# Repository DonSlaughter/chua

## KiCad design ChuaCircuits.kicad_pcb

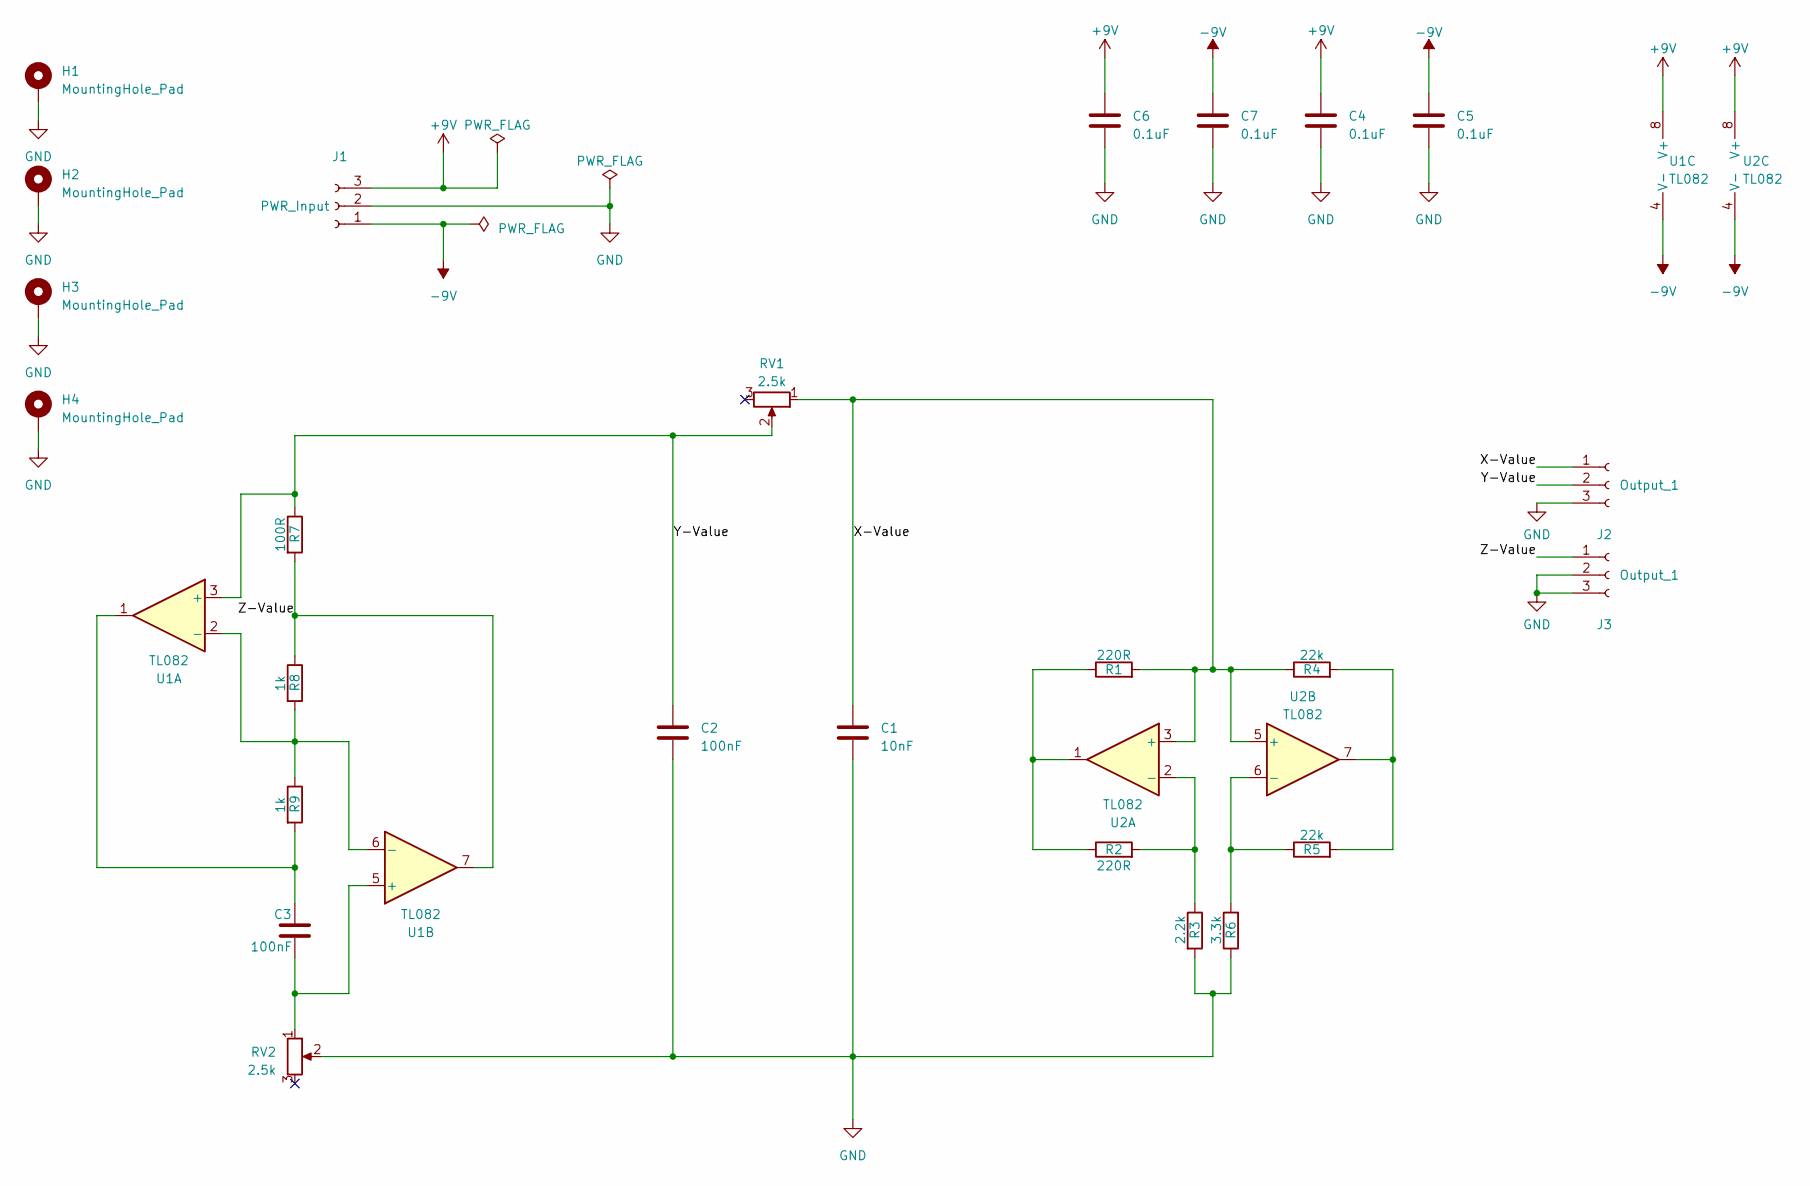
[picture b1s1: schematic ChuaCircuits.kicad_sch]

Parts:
C1: 10nF; C_Disc_D7.5mm_W5.0mm_P7.50mm
C2, C3: 100nF; C_Disc_D7.5mm_W5.0mm_P7.50mm
C4, C5, C6, C7: 0.1uF; C_Disc_D3.8mm_W2.6mm_P2.50mm
H1, H2, H3, H4: MountingHole_Pad; MountingHole_2.7mm_M2.5_DIN965_Pad
J1: PWR_Input; 1985205
J2, J3: Output_1; 1985205
R1, R2: 220R; R_Axial_DIN0207_L6.3mm_D2.5mm_P10.16mm_Horizontal
R3: 2.2k; R_Axial_DIN0207_L6.3mm_D2.5mm_P10.16mm_Horizontal
R4, R5: 22k; R_Axial_DIN0207_L6.3mm_D2.5mm_P10.16mm_Horizontal
R6: 3.3k; R_Axial_DIN0207_L6.3mm_D2.5mm_P10.16mm_Horizontal
R7: 100R; R_Axial_DIN0207_L6.3mm_D2.5mm_P10.16mm_Horizontal
R8, R9: 1k; R_Axial_DIN0207_L6.3mm_D2.5mm_P10.16mm_Horizontal
RV1, RV2: 2.5k; Potentiometer_Bourns_3266W_Vertical
U1, U2: TL082; DIP-8_W7.62mm

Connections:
+9V: C4.1, C6.1, J1.3, U1.8 (V+), U2.8 (V+)
-9V: C5.1, C7.1, J1.1, U1.4 (V-), U2.4 (V-)
/X-Value: C1.1, J2.1, R1.2, R4.1, RV1.1, U2.3 (+), U2.5 (+)
/Y-Value: C2.1, J2.2, R7.1, RV1.2, U1.3 (+)
/Z-Value: J3.1, R7.2, R8.1, U1.7
GND: C1.2, C2.2, C4.2, C5.2, C6.2, C7.2, H1.1, H2.1, H3.1, H4.1, J1.2, J2.3, J3.2, J3.3, R3.2, R6.1, RV2.2
unnamed: C3.1, R9.2, U1.1
unnamed: R1.1, R2.1, U2.1
unnamed: R4.2, R5.2, U2.7
unnamed: R8.2, R9.1, U1.2 (-), U1.6 (-)
unnamed: C3.2, RV2.1, U1.5 (+)
unnamed: R2.2, R3.1, U2.2 (-)
unnamed: R5.1, R6.2, U2.6 (-)

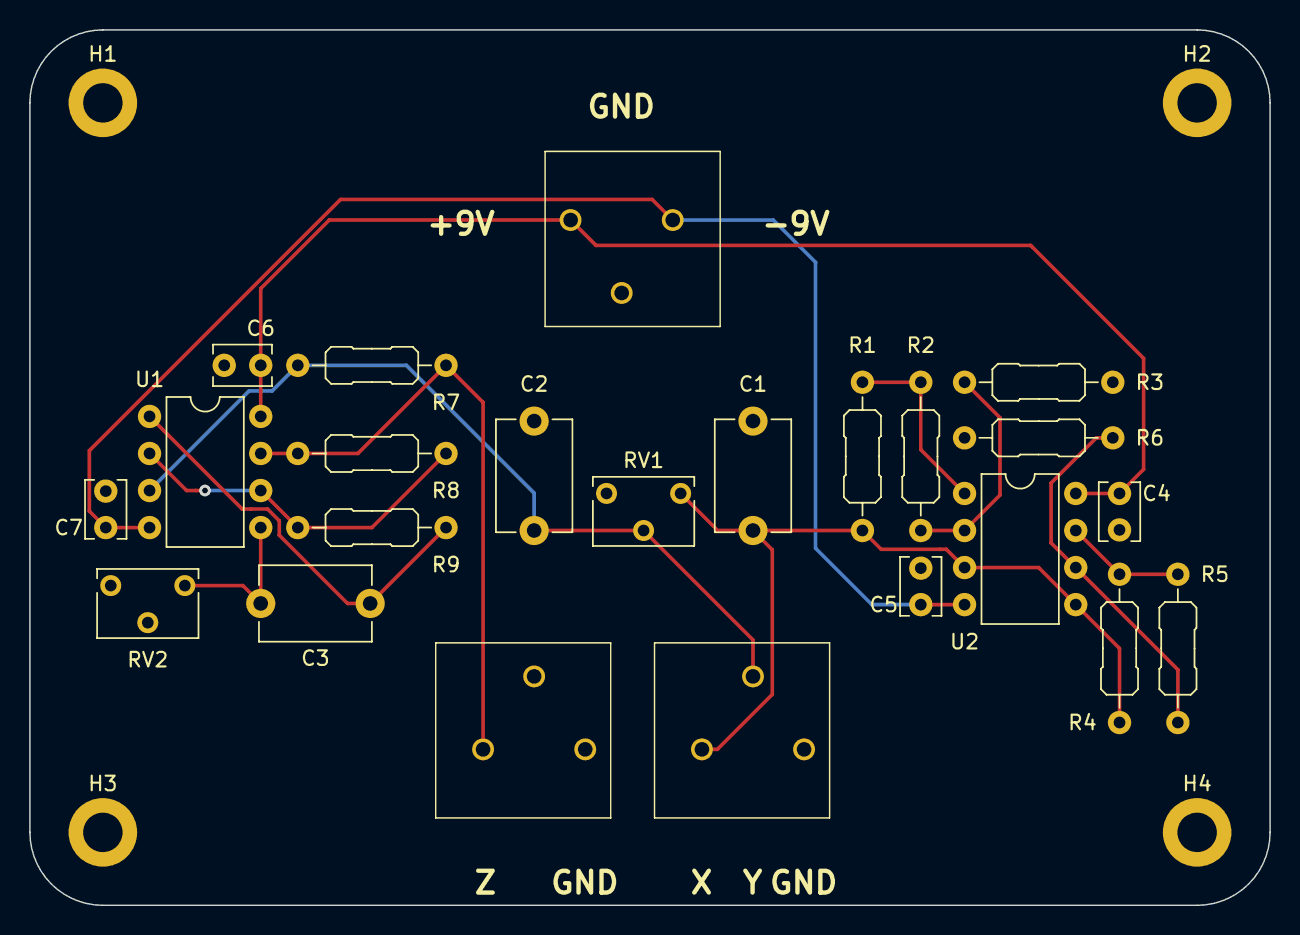
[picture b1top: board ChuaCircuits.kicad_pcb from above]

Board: 2 copper layers, 85.0 x 60.0 mm, 27 parts (0 on the bottom side), 13 nets.

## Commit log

2023-04-27 gitignore
2023-04-27 kicad files added
2023-04-28 first connection tests
2023-05-01 finished board v1
